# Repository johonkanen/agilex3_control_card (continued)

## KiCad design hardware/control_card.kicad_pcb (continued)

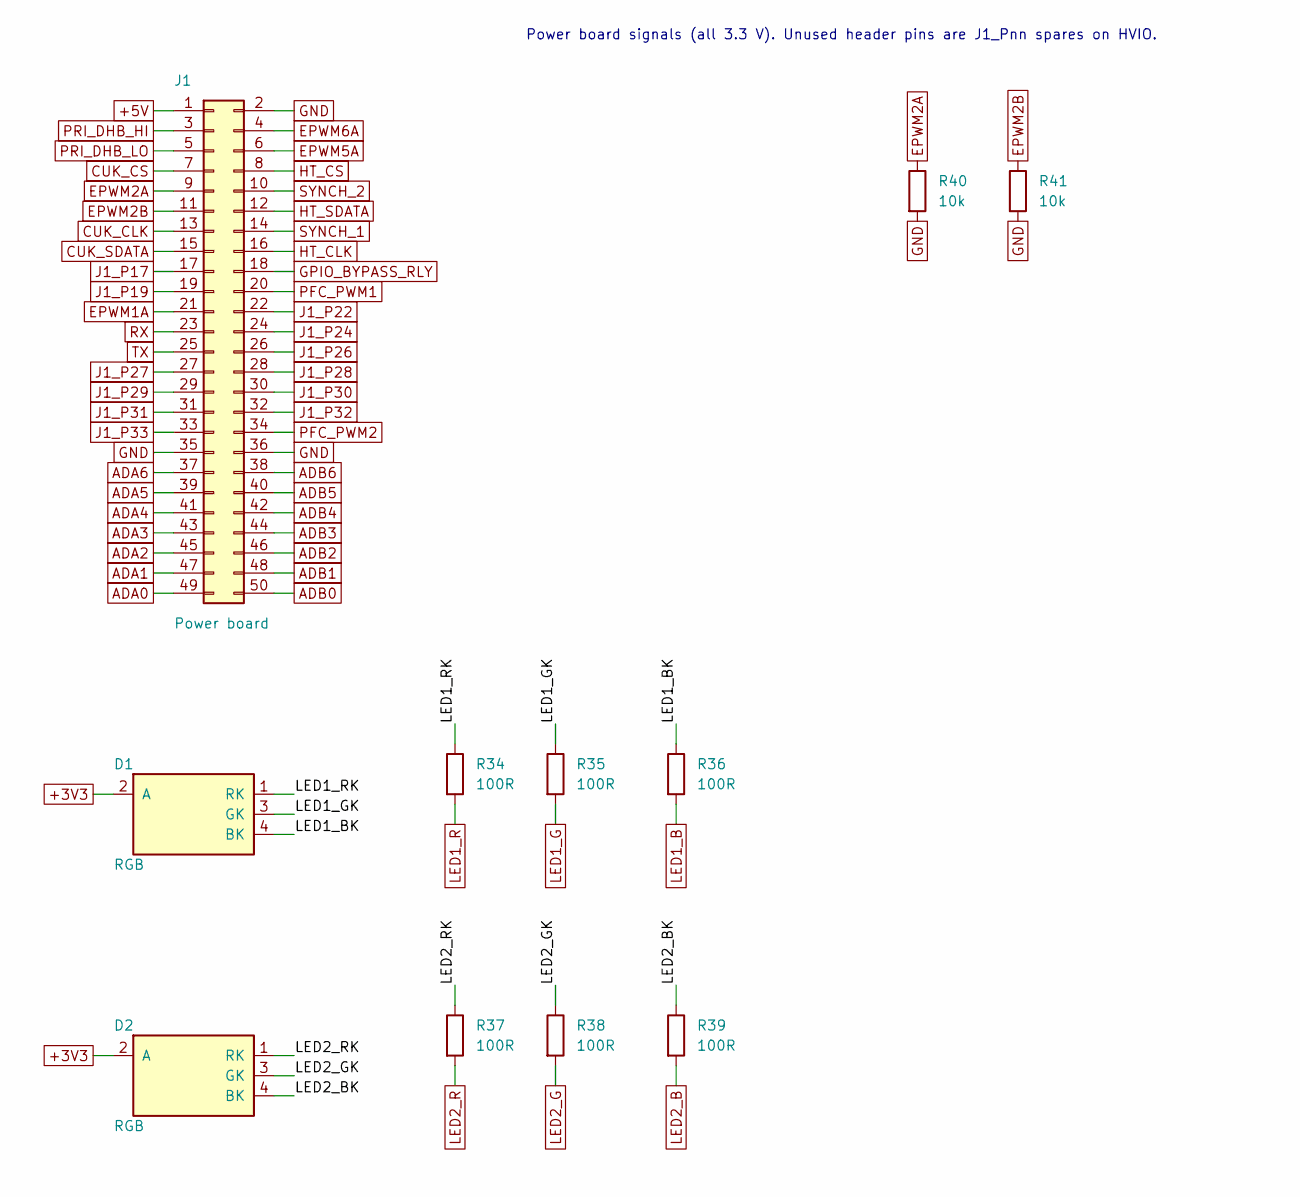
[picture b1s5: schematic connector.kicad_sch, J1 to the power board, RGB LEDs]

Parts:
D1, D2: RGB; LED_RGB_APFA3010_RightAngle; MPN APFA3010LSEEZGKQBKC; LCSC C5393554
J1: Power board; PinHeader_2x25_P1.27mm_Horizontal_U25
R34, R35, R36, R37, R38, R39: 100R; R_0402_1005Metric; MPN 0402WGF1000TCE; LCSC C25076
R40, R41: 10k; R_0201_0603Metric; MPN 0201WMF1002TEE; LCSC C473048

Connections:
+3V3: D1.2 (A), D2.2 (A); also elsewhere on the board
+5V: J1.1; also elsewhere on the board
/Header and LEDs/LED1_BK: D1.4 (BK), R36.1
/Header and LEDs/LED1_GK: D1.3 (GK), R35.1
/Header and LEDs/LED1_RK: D1.1 (RK), R34.1
/Header and LEDs/LED2_BK: D2.4 (BK), R39.1
/Header and LEDs/LED2_GK: D2.3 (GK), R38.1
/Header and LEDs/LED2_RK: D2.1 (RK), R37.1
ADA0: J1.49; also elsewhere on the board
ADA1: J1.47; also elsewhere on the board
ADA2: J1.45; also elsewhere on the board
ADA3: J1.43; also elsewhere on the board
ADA4: J1.41; also elsewhere on the board
ADA5: J1.39; also elsewhere on the board
ADA6: J1.37; also elsewhere on the board
ADB0: J1.50; also elsewhere on the board
ADB1: J1.48; also elsewhere on the board
ADB2: J1.46; also elsewhere on the board
ADB3: J1.44; also elsewhere on the board
ADB4: J1.42; also elsewhere on the board
ADB5: J1.40; also elsewhere on the board
ADB6: J1.38; also elsewhere on the board
CUK_CLK: J1.13; also elsewhere on the board
CUK_CS: J1.7; also elsewhere on the board
CUK_SDATA: J1.15; also elsewhere on the board
EPWM1A: J1.21; also elsewhere on the board
EPWM2A: J1.9, R40.1; also elsewhere on the board
EPWM2B: J1.11, R41.1; also elsewhere on the board
EPWM5A: J1.6; also elsewhere on the board
EPWM6A: J1.4; also elsewhere on the board
GND: J1.2, J1.35, J1.36, R40.2, R41.2; also elsewhere on the board
GPIO_BYPASS_RLY: J1.18; also elsewhere on the board
HT_CLK: J1.16; also elsewhere on the board
HT_CS: J1.8; also elsewhere on the board
HT_SDATA: J1.12; also elsewhere on the board
J1_P17: J1.17; also elsewhere on the board
J1_P19: J1.19; also elsewhere on the board
J1_P22: J1.22; also elsewhere on the board
J1_P24: J1.24; also elsewhere on the board
J1_P26: J1.26; also elsewhere on the board
J1_P27: J1.27; also elsewhere on the board
J1_P28: J1.28; also elsewhere on the board
J1_P29: J1.29; also elsewhere on the board
J1_P30: J1.30; also elsewhere on the board
J1_P31: J1.31; also elsewhere on the board
J1_P32: J1.32; also elsewhere on the board
J1_P33: J1.33; also elsewhere on the board
LED1_B: R36.2; also elsewhere on the board
LED1_G: R35.2; also elsewhere on the board
LED1_R: R34.2; also elsewhere on the board
LED2_B: R39.2; also elsewhere on the board
LED2_G: R38.2; also elsewhere on the board
LED2_R: R37.2; also elsewhere on the board
PFC_PWM1: J1.20; also elsewhere on the board
PFC_PWM2: J1.34; also elsewhere on the board
PRI_DHB_HI: J1.3; also elsewhere on the board
PRI_DHB_LO: J1.5; also elsewhere on the board
RX: J1.23; also elsewhere on the board
SYNCH_1: J1.14; also elsewhere on the board
SYNCH_2: J1.10; also elsewhere on the board
TX: J1.25; also elsewhere on the board

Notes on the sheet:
Power board signals (all 3.3 V). Unused header pins are J1_Pnn spares on HVIO.

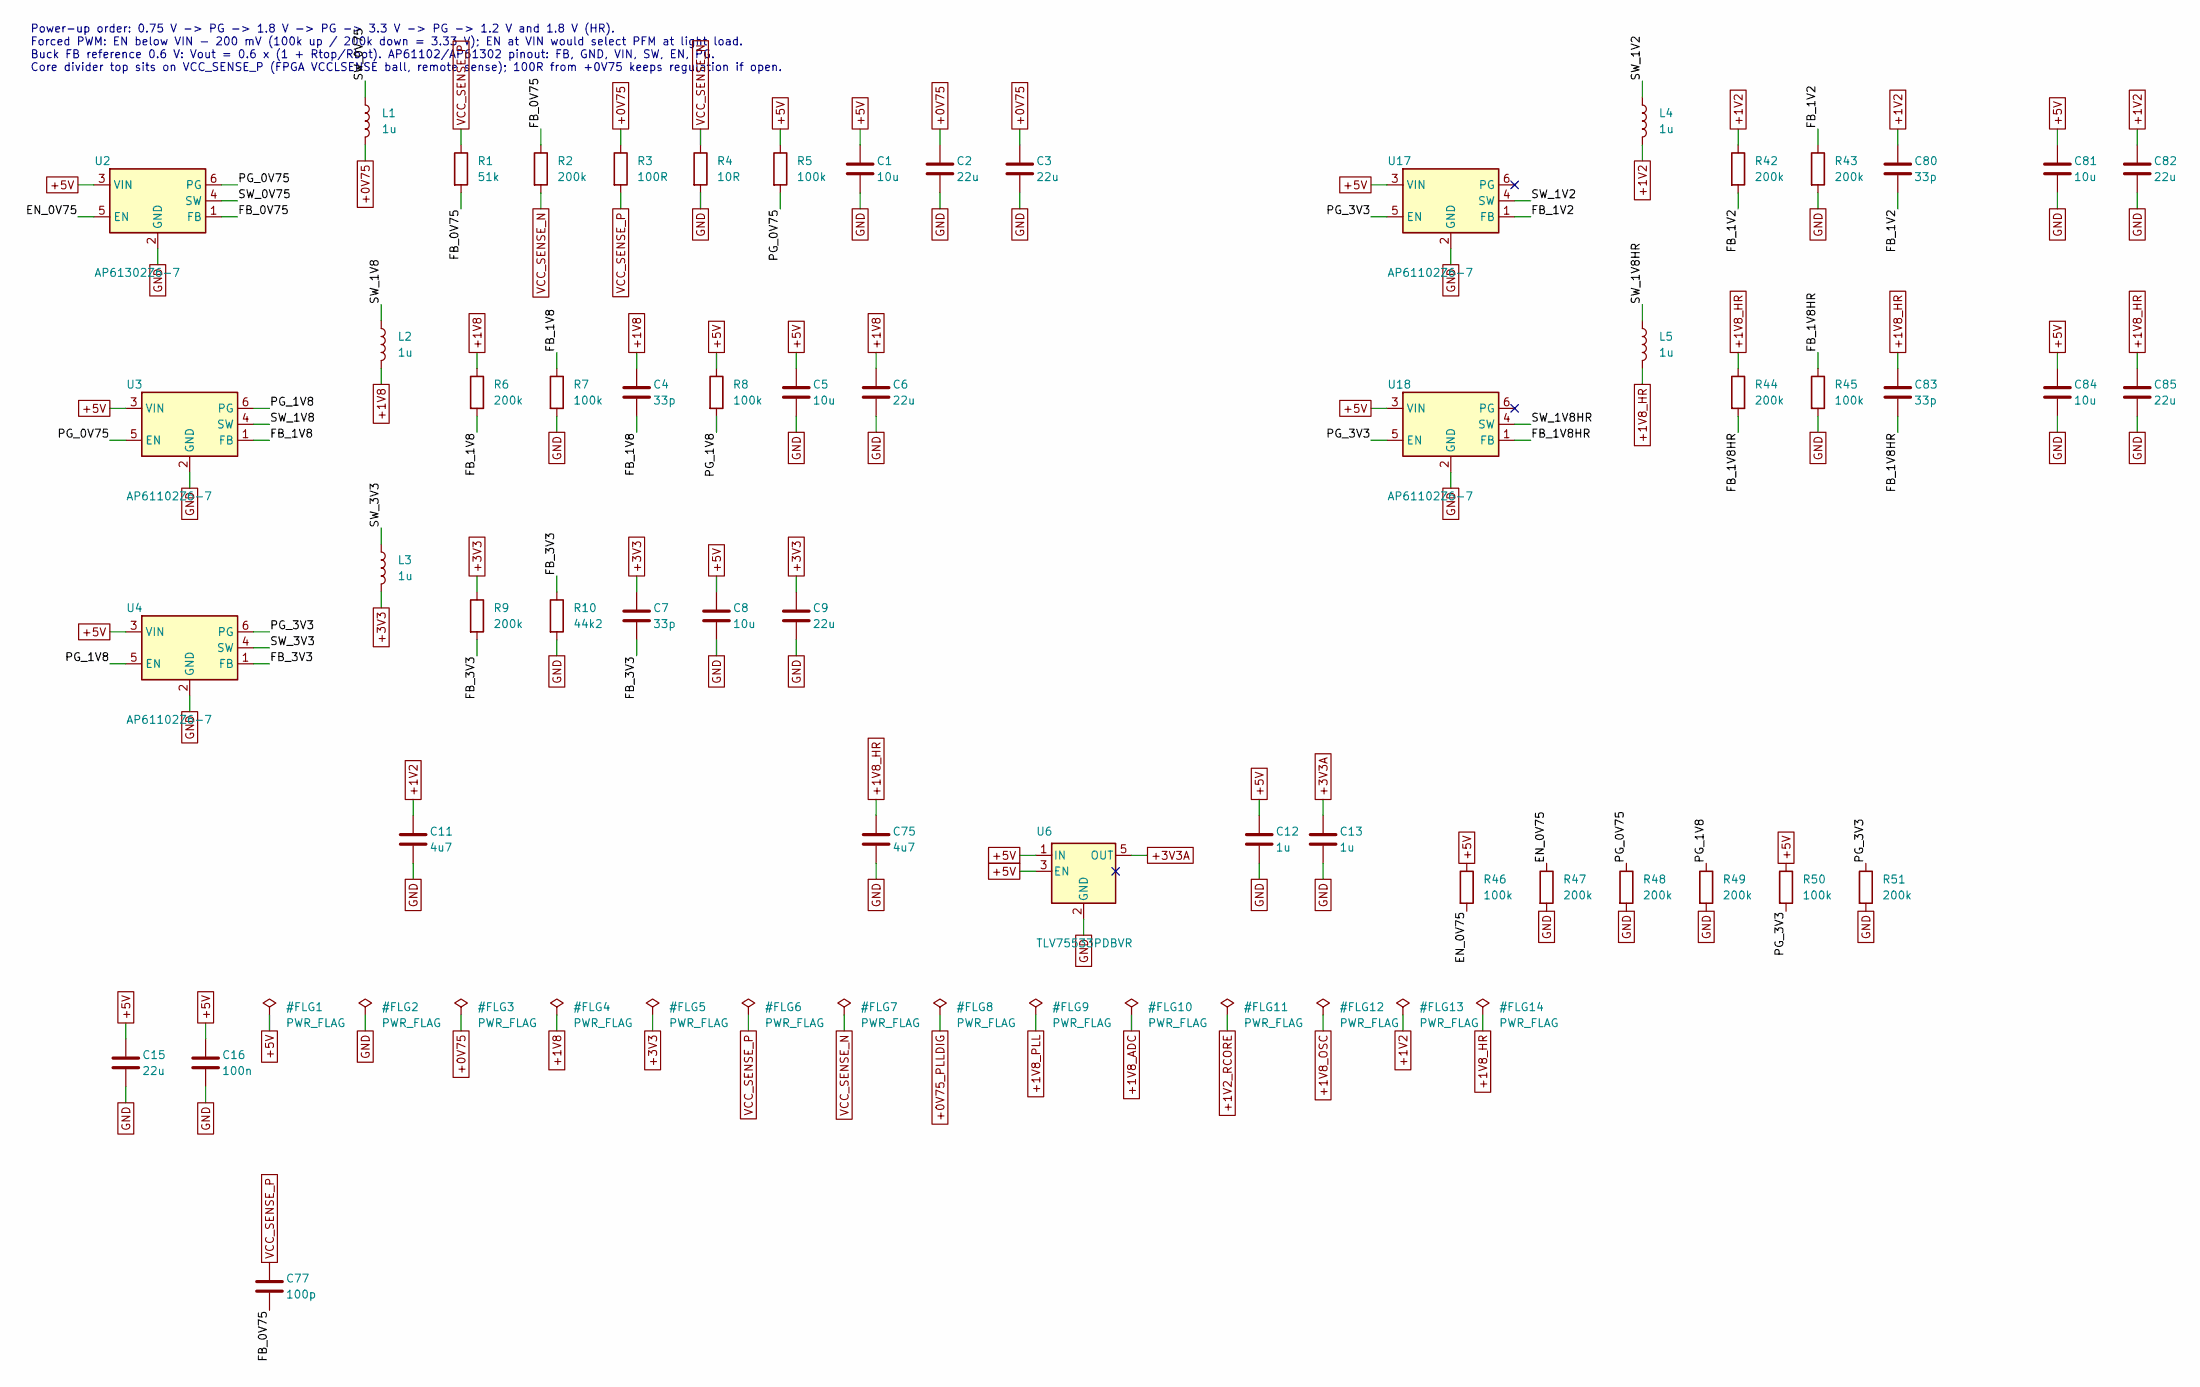
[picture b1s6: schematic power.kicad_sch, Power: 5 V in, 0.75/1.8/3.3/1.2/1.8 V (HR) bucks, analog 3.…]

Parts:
C1, C5, C8, C81, C84: 10u; C_0603_1608Metric; MPN CL10A106KP8NNNC; LCSC C19702
C2, C3, C6, C9, C82, C85: 22u; C_0603_1608Metric; MPN CL10A226MQ8NRNC; LCSC C59461
C4, C7, C80, C83: 33p; C_0402_1005Metric; MPN 0402CG330J500NT; LCSC C1562
C11, C75: 4u7; C_0603_1608Metric; MPN CL10A475KO8NNNC; LCSC C19666
C12, C13: 1u; C_0402_1005Metric; MPN CL05A105KA5NQNC; LCSC C52923
C15: 22u; C_0805_2012Metric; MPN CL21A226MAQNNNE; LCSC C45783
C16: 100n; C_0402_1005Metric; MPN CL05B104KO5NNNC; LCSC C1525
C77: 100p; C_0402_1005Metric; MPN 0402CG101J500NT; LCSC C1546
L1, L2, L3, L4, L5: 1u; L_Cenker_CKCS201610; MPN WPN201610H1R0MT; LCSC C97002
R1: 51k; R_0402_1005Metric; MPN 0402WGF5102TCE; LCSC C25794
R2, R6, R9, R42, R43, R44, R47, R48, R49, R51: 200k; R_0402_1005Metric; MPN 0402WGF2003TCE; LCSC C25764
R3: 100R; R_0402_1005Metric; MPN 0402WGF1000TCE; LCSC C25076
R4: 10R; R_0402_1005Metric; MPN 0402WGF100JTCE; LCSC C25077
R5, R7, R8, R45, R50: 100k; R_0402_1005Metric; MPN 0402WGF1003TCE; LCSC C25741
R10: 44k2; R_0402_1005Metric; MPN 0402WGF4422TCE; LCSC C25895
R46: 100k; R_0201_0603Metric; MPN RC0201FR-07100KL; LCSC C106224
U2: AP61302Z6-7; SOT-563; MPN AP61302Z6-7; LCSC C3193204
U3, U4, U17, U18: AP61102Z6-7; SOT-563; MPN AP61102Z6-7; LCSC C5224055
U6: TLV75533PDBVR; SOT-23-5; MPN TLV75533PDBVR; LCSC C404027

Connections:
+0V75: C2.1, C3.1, L1.2, R3.1; also elsewhere on the board
+1V2: C11.1, C80.1, C82.1, L4.2, R42.1; also elsewhere on the board
+1V8: C4.1, C6.1, L2.2, R6.1; also elsewhere on the board
+1V8_HR: C75.1, C83.1, C85.1, L5.2, R44.1; also elsewhere on the board
+3V3: C7.1, C9.1, L3.2, R9.1; also elsewhere on the board
+3V3A: C13.1, U6.5 (OUT); also elsewhere on the board
+5V: C1.1, C5.1, C8.1, C12.1, C15.1, C16.1, C81.1, C84.1, R5.1, R8.1, R46.1, R50.1, U2.3 (VIN), U3.3 (VIN), U4.3 (VIN), U6.1 (IN), U6.3 (EN), U17.3 (VIN), U18.3 (VIN); also elsewhere on the board
/Power/EN_0V75: R46.2, R47.1, U2.5 (EN)
/Power/FB_0V75: C77.2, R1.2, R2.1, U2.1 (FB)
/Power/FB_1V2: C80.2, R42.2, R43.1, U17.1 (FB)
/Power/FB_1V8: C4.2, R6.2, R7.1, U3.1 (FB)
/Power/FB_1V8HR: C83.2, R44.2, R45.1, U18.1 (FB)
/Power/FB_3V3: C7.2, R9.2, R10.1, U4.1 (FB)
/Power/PG_0V75: R5.2, R48.1, U2.6 (PG), U3.5 (EN)
/Power/PG_1V8: R8.2, R49.1, U3.6 (PG), U4.5 (EN)
/Power/PG_3V3: R50.2, R51.1, U4.6 (PG), U17.5 (EN), U18.5 (EN)
/Power/SW_0V75: L1.1, U2.4 (SW)
/Power/SW_1V2: L4.1, U17.4 (SW)
/Power/SW_1V8: L2.1, U3.4 (SW)
/Power/SW_1V8HR: L5.1, U18.4 (SW)
/Power/SW_3V3: L3.1, U4.4 (SW)
GND: C1.2, C2.2, C3.2, C5.2, C6.2, C8.2, C9.2, C11.2, C12.2, C13.2, C15.2, C16.2, C75.2, C81.2, C82.2, C84.2, C85.2, R4.2, R7.2, R10.2, R43.2, R45.2, R47.2, R48.2, R49.2, R51.2, U2.2 (GND), U3.2 (GND), U4.2 (GND), U6.2 (GND), U17.2 (GND), U18.2 (GND); also elsewhere on the board
VCC_SENSE_N: R2.2, R4.1; also elsewhere on the board
VCC_SENSE_P: C77.1, R1.1, R3.2; also elsewhere on the board

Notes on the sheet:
Power-up order: 0.75 V -> PG -> 1.8 V -> PG -> 3.3 V -> PG -> 1.2 V and 1.8 V (HR). Forced PWM: EN below VIN - 200 mV (100k up / 200k down = 3.33 V); EN at VIN would select PFM at light load. Buck FB reference 0.6 V: Vout = 0.6 x (1 + Rtop/Rbot). AP61102/AP61302 pinout: FB, GND, VIN, SW, EN, PG. Co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

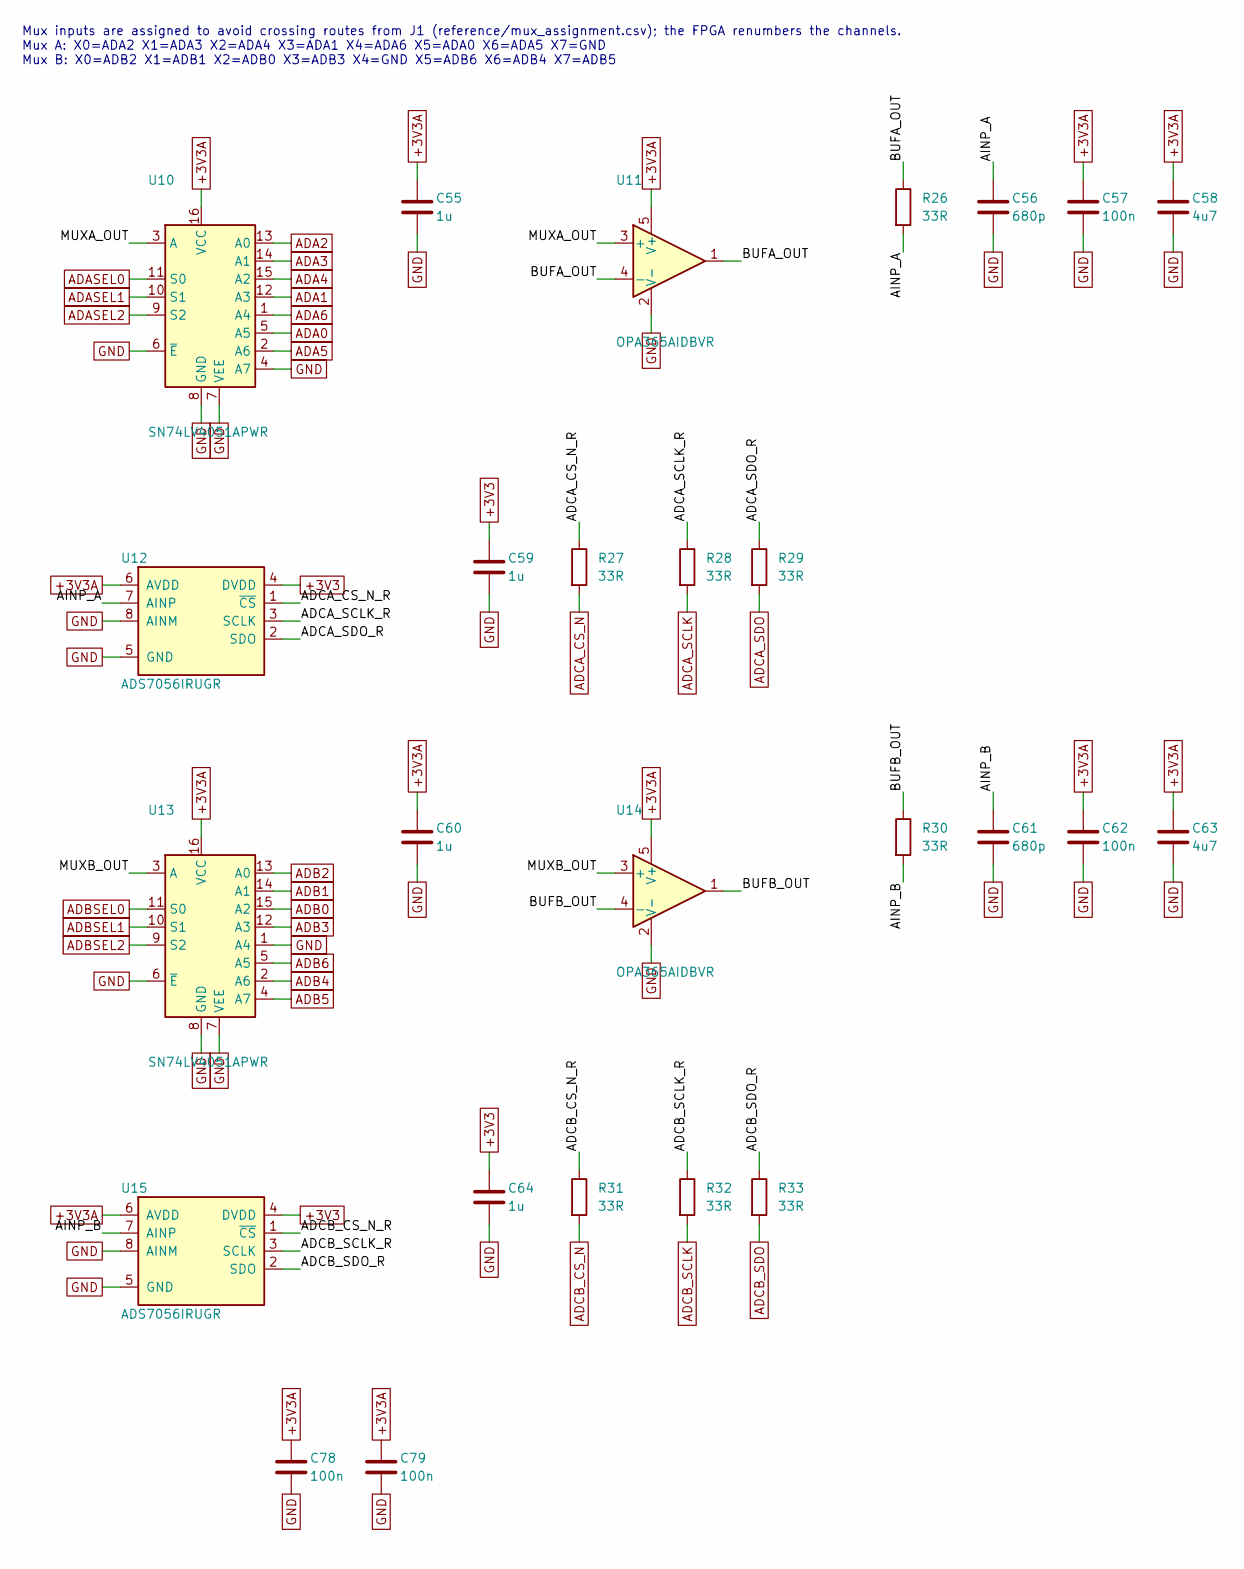
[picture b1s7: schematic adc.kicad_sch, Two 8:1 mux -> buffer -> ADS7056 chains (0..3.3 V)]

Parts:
C55, C59, C60, C64: 1u; C_0402_1005Metric; MPN CL05A105KA5NQNC; LCSC C52923
C56, C61: 680p; C_0402_1005Metric; MPN CC0402JRNPO9BN681; LCSC C113781
C57, C62, C78, C79: 100n; C_0402_1005Metric; MPN CL05B104KO5NNNC; LCSC C1525
C58, C63: 4u7; C_0603_1608Metric; MPN CL10A475KO8NNNC; LCSC C19666
R26, R30: 33R; R_0402_1005Metric; MPN 0402WGF330JTCE; LCSC C25105
R27, R28, R29, R32, R33: 33R; R_0201_0603Metric; MPN RC-01W33R0FT; LCSC C320843
R31: 33R; C_0201_0603Metric; MPN RC-01W33R0FT; LCSC C320843
U10, U13: SN74LV4051APWR; TSSOP-16_4.4x5mm_P0.65mm; MPN SN74LV4051APWR; LCSC C7793
U11, U14: OPA365AIDBVR; SOT-23-5; MPN OPA365AIDBVR; LCSC C96626
U12, U15: ADS7056IRUGR; Texas_UQFN-8_1.5x1.5mm_P0.5mm; MPN ADS7056IRUGR; LCSC C2669798

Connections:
+3V3: C59.1, C64.1, U12.4 (DVDD), U15.4 (DVDD); also elsewhere on the board
+3V3A: C55.1, C57.1, C58.1, C60.1, C62.1, C63.1, C78.1, C79.1, U10.16 (VCC), U11.5 (V+), U12.6 (AVDD), U13.16 (VCC), U14.5 (V+), U15.6 (AVDD); also elsewhere on the board
/ADC/ADCA_CS_N_R: R27.1, U12.1 (~CS)
/ADC/ADCA_SCLK_R: R28.1, U12.3 (SCLK)
/ADC/ADCA_SDO_R: R29.1, U12.2 (SDO)
/ADC/ADCB_CS_N_R: R31.1, U15.1 (~CS)
/ADC/ADCB_SCLK_R: R32.1, U15.3 (SCLK)
/ADC/ADCB_SDO_R: R33.1, U15.2 (SDO)
/ADC/AINP_A: C56.1, R26.2, U12.7 (AINP)
/ADC/AINP_B: C61.1, R30.2, U15.7 (AINP)
/ADC/BUFA_OUT: R26.1, U11.1, U11.4 (-)
/ADC/BUFB_OUT: R30.1, U14.1, U14.4 (-)
/ADC/MUXA_OUT: U10.3 (A), U11.3 (+)
/ADC/MUXB_OUT: U13.3 (A), U14.3 (+)
ADA0: U10.5 (A5); also elsewhere on the board
ADA1: U10.12 (A3); also elsewhere on the board
ADA2: U10.13 (A0); also elsewhere on the board
ADA3: U10.14 (A1); also elsewhere on the board
ADA4: U10.15 (A2); also elsewhere on the board
ADA5: U10.2 (A6); also elsewhere on the board
ADA6: U10.1 (A4); also elsewhere on the board
ADASEL0: U10.11 (S0); also elsewhere on the board
ADASEL1: U10.10 (S1); also elsewhere on the board
ADASEL2: U10.9 (S2); also elsewhere on the board
ADB0: U13.15 (A2); also elsewhere on the board
ADB1: U13.14 (A1); also elsewhere on the board
ADB2: U13.13 (A0); also elsewhere on the board
ADB3: U13.12 (A3); also elsewhere on the board
ADB4: U13.2 (A6); also elsewhere on the board
ADB5: U13.4 (A7); also elsewhere on the board
ADB6: U13.5 (A5); also elsewhere on the board
ADBSEL0: U13.11 (S0); also elsewhere on the board
ADBSEL1: U13.10 (S1); also elsewhere on the board
ADBSEL2: U13.9 (S2); also elsewhere on the board
ADCA_CS_N: R27.2; also elsewhere on the board
ADCA_SCLK: R28.2; also elsewhere on the board
ADCA_SDO: R29.2; also elsewhere on the board
ADCB_CS_N: R31.2; also elsewhere on the board
ADCB_SCLK: R32.2; also elsewhere on the board
ADCB_SDO: R33.2; also elsewhere on the board
GND: C55.2, C56.2, C57.2, C58.2, C59.2, C60.2, C61.2, C62.2, C63.2, C64.2, C78.2, C79.2, U10.4 (A7), U10.6 (~E), U10.7 (VEE), U10.8 (GND), U11.2 (V-), U12.5 (GND), U12.8 (AINM), U13.1 (A4), U13.6 (~E), U13.7 (VEE), U13.8 (GND), U14.2 (V-), U15.5 (GND), U15.8 (AINM); also elsewhere on the board

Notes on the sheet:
Mux inputs are assigned to avoid crossing routes from J1 (reference/mux_assignment.csv); the FPGA renumbers the channels. Mux A: X0=ADA2 X1=ADA3 X2=ADA4 X3=ADA1 X4=ADA6 X5=ADA0 X6=ADA5 X7=GND Mux B: X0=ADB2 X1=ADB1 X2=ADB0 X3=ADB3 X4=GND X5=ADB6 X6=ADB4 X7=ADB5

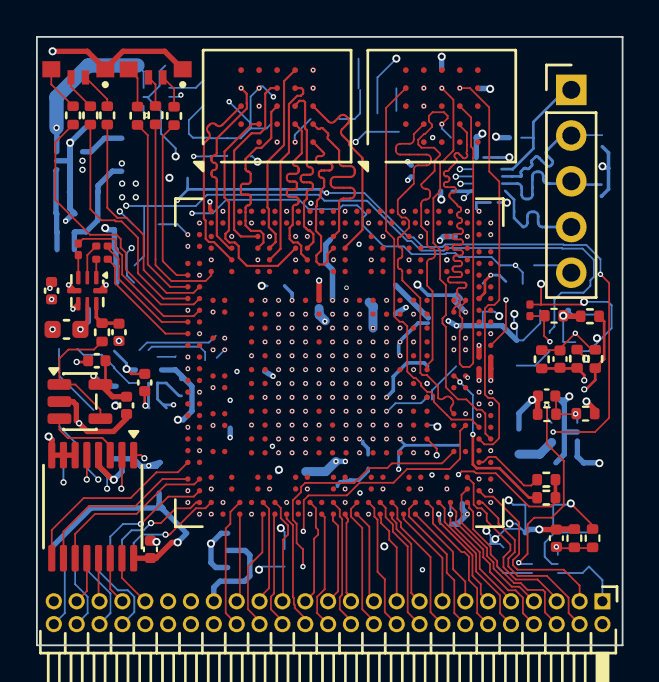
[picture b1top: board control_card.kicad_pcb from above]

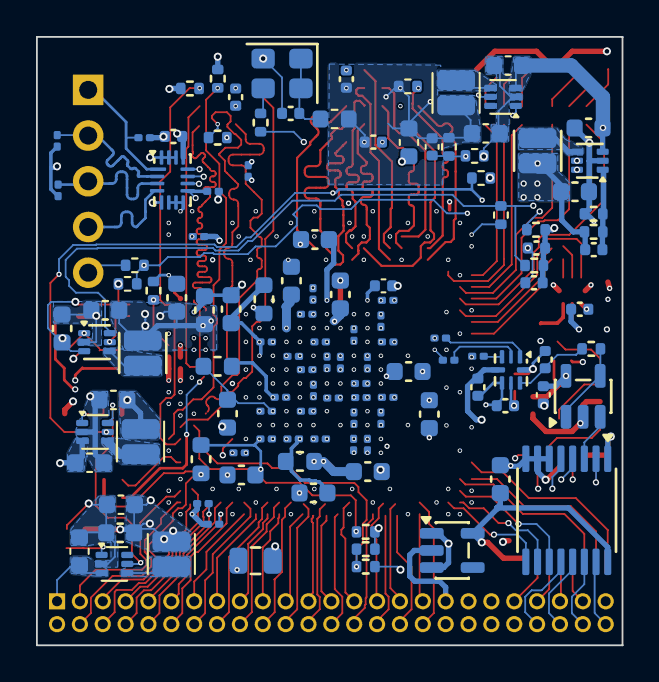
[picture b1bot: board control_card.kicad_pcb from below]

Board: 6 copper layers, 32.5 x 33.8 mm, 164 parts (122 on the bottom side), 145 nets.

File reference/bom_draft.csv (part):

ref,value,footprint,lcsc,mpn,dnp
C1,10u,Capacitor_SMD:C_0603_1608Metric,C19702,CL10A106KP8NNNC,False
C2,22u,Capacitor_SMD:C_0603_1608Metric,C59461,CL10A226MQ8NRNC,False
C3,22u,Capacitor_SMD:C_0603_1608Metric,C59461,CL10A226MQ8NRNC,False
C4,22p,Capacitor_SMD:C_0402_1005Metric,C1555,0402CG220J500NT,False
C5,10u,Capacitor_SMD:C_0603_1608Metric,C19702,CL10A106KP8NNNC,False
C6,22u,Capacitor_SMD:C_0603_1608Metric,C59461,CL10A226MQ8NRNC,False
C7,22p,Capacitor_SMD:C_0402_1005Metric,C1555,0402CG220J500NT,False
C8,10u,Capacitor_SMD:C_0603_1608Metric,C19702,CL10A106KP8NNNC,False
C9,22u,Capacitor_SMD:C_0603_1608Metric,C59461,CL10A226MQ8NRNC,False
C10,1u,Capacitor_SMD:C_0402_1005Metric,C52923,CL05A105KA5NQNC,False
C11,4u7,Capacitor_SMD:C_0603_1608Metric,C19666,CL10A475KO8NNNC,False
C12,1u,Capacitor_SMD:C_0402_1005Metric,C52923,CL05A105KA5NQNC,False
C13,1u,Capacitor_SMD:C_0402_1005Metric,C52923,CL05A105KA5NQNC,False
C14,22u,Capacitor_SMD:C_0805_2012Metric,C45783,CL21A226MAQNNNE,False
C15,22u,Capacitor_SMD:C_0805_2012Metric,C45783,CL21A226MAQNNNE,False
C16,100n,Capacitor_SMD:C_0402_1005Metric,C1525,CL05B104KO5NNNC,False
C17,22u,Capacitor_SMD:C_0603_1608Metric,C59461,CL10A226MQ8NRNC,False
C18,22u,Capacitor_SMD:C_0603_1608Metric,C59461,CL10A226MQ8NRNC,False
C19,10u,Capacitor_SMD:C_0603_1608Metric,C19702,CL10A106KP8NNNC,False
C20,10u,Capacitor_SMD:C_0603_1608Metric,C19702,CL10A106KP8NNNC,False
C21,4u7,Capacitor_SMD:C_0201_0603Metric,C335103,GRM035R60J475ME15D,False
C22,4u7,Capacitor_SMD:C_0201_0603Metric,C335103,GRM035R60J475ME15D,False
C23,4u7,Capacitor_SMD:C_0201_0603Metric,C335103,GRM035R60J475ME15D,False
C24,1u,Capacitor_SMD:C_0201_0603Metric,C170152,CL03A105MQ3CSNC,False
C25,1u,Capacitor_SMD:C_0201_0603Metric,C170152,CL03A105MQ3CSNC,False
C26,1u,Capacitor_SMD:C_0201_0603Metric,C170152,CL03A105MQ3CSNC,False
C27,1u,Capacitor_SMD:C_0201_0603Metric,C170152,CL03A105MQ3CSNC,False
C28,1u,Capacitor_SMD:C_0201_0603Metric,C170152,CL03A105MQ3CSNC,False
C29,10u,Capacitor_SMD:C_0603_1608Metric,C19702,CL10A106KP8NNNC,False
C30,4u7,Capacitor_SMD:C_0201_0603Metric,C335103,GRM035R60J475ME15D,False
C31,4u7,Capacitor_SMD:C_0201_0603Metric,C335103,GRM035R60J475ME15D,False
C32,1u,Capacitor_SMD:C_0201_0603Metric,C170152,CL03A105MQ3CSNC,False
C33,1u,Capacitor_SMD:C_0201_0603Metric,C170152,CL03A105MQ3CSNC,False
C34,1u,Capacitor_SMD:C_0201_0603Metric,C170152,CL03A105MQ3CSNC,False
C35,1u,Capacitor_SMD:C_0201_0603Metric,C170152,CL03A105MQ3CSNC,False
C36,1u,Capacitor_SMD:C_0201_0603Metric,C170152,CL03A105MQ3CSNC,False
C37,10u,Capacitor_SMD:C_0603_1608Metric,C19702,CL10A106KP8NNNC,False
C38,1u,Capacitor_SMD:C_0201_0603Metric,C170152,CL03A105MQ3CSNC,False
C39,1u,Capacitor_SMD:C_0201_0603Metric,C170152,CL03A105MQ3CSNC,False
C40,1u,Capacitor_SMD:C_0201_0603Metric,C170152,CL03A105MQ3CSNC,False
C41,1u,Capacitor_SMD:C_0201_0603Metric,C170152,CL03A105MQ3CSNC,False
C42,1u,Capacitor_SMD:C_0201_0603Metric,C170152,CL03A105MQ3CSNC,False
C43,1u,Capacitor_SMD:C_0201_0603Metric,C170152,CL03A105MQ3CSNC,False
C44,4u7,Capacitor_SMD:C_0603_1608Metric,C19666,CL10A475KO8NNNC,False
C45,4u7,Capacitor_SMD:C_0201_0603Metric,C335103,GRM035R60J475ME15D,False
C46,1u,Capacitor_SMD:C_0201_0603Metric,C170152,CL03A105MQ3CSNC,False
C47,100n,Capacitor_SMD:C_0402_1005Metric,C1525,CL05B104KO5NNNC,False
C48,1u,Capacitor_SMD:C_0402_1005Metric,C52923,CL05A105KA5NQNC,False
C49,100n,Capacitor_SMD:C_0201_0603Metric,C49062,CL03A104KP3NNNC,False
C50,100n,Capacitor_SMD:C_0201_0603Metric,C49062,CL03A104KP3NNNC,False
C51,100n,Capacitor_SMD:C_0402_1005Metric,C1525,CL05B104KO5NNNC,False
C52,100n,Capacitor_SMD:C_0402_1005Metric,C1525,CL05B104KO5NNNC,False
C53,1u,Capacitor_SMD:C_0402_1005Metric,C52923,CL05A105KA5NQNC,False
C54,470n,Capacitor_SMD:C_0402_1005Metric,C47339,CL05A474KP5NNNC,False
C55,1u,Capacitor_SMD:C_0402_1005Metric,C52923,CL05A105KA5NQNC,False
C56,680p,Capacitor_SMD:C_0402_1005Metric,C301953,0402CG681J500NT,False
C57,100n,Capacitor_SMD:C_0402_1005Metric,C1525,CL05B104KO5NNNC,False
C58,4u7,Capacitor_SMD:C_0603_1608Metric,C19666,CL10A475KO8NNNC,False
C59,1u,Capacitor_SMD:C_0402_1005Metric,C52923,CL05A105KA5NQNC,False
C60,1u,Capacitor_SMD:C_0402_1005Metric,C52923,CL05A105KA5NQNC,False
C61,680p,Capacitor_SMD:C_0402_1005Metric,C301953,0402CG681J500NT,False
C62,100n,Capacitor_SMD:C_0402_1005Metric,C1525,CL05B104KO5NNNC,False
C63,4u7,Capacitor_SMD:C_0603_1608Metric,C19666,CL10A475KO8NNNC,False
C64,1u,Capacitor_SMD:C_0402_1005Metric,C52923,CL05A105KA5NQNC,False
C65,47u,Capacitor_SMD:C_0603_1608Metric,C6119831,CGA0603X5R476M6R3JT,False
C66,1u,Capacitor_SMD:C_0201_0603Metric,C170152,CL03A105MQ3CSNC,False
C67,47u,Capacitor_SMD:C_0603_1608Metric,C6119831,CGA0603X5R476M6R3JT,False
C68,1u,Capacitor_SMD:C_0201_0603Metric,C170152,CL03A105MQ3CSNC,False
C69,47u,Capacitor_SMD:C_0603_1608Metric,C6119831,CGA0603X5R476M6R3JT,False
C70,1u,Capacitor_SMD:C_0201_0603Metric,C170152,CL03A105MQ3CSNC,False
C71,47u,Capacitor_SMD:C_0603_1608Metric,C6119831,CGA0603X5R476M6R3JT,False
C72,1u,Capacitor_SMD:C_0201_0603Metric,C170152,CL03A105MQ3CSNC,False
C73,1u,Capacitor_SMD:C_0201_0603Metric,C170152,CL03A105MQ3CSNC,False
C74,1u,Capacitor_SMD:C_0402_1005Metric,C52923,CL05A105KA5NQNC,False
C75,4u7,Capacitor_SMD:C_0603_1608Metric,C19666,CL10A475KO8NNNC,False
C76,1u,Capacitor_SMD:C_0201_0603Metric,C170152,CL03A105MQ3CSNC,False
D1,RGB,control_card:LED_RGB_APFA3010_RightAngle,C5393554,APFA3010LSEEZGKQBKC,False
D2,RGB,control_card:LED_RGB_APFA3010_RightAngle,C5393554,APFA3010LSEEZGKQBKC,False
FB1,120R@100MHz,Inductor_SMD:L_0603_1608Metric,C14709,BLM18PG121SN1D,False
FB2,120R@100MHz,Inductor_SMD:L_0603_1608Metric,C14709,BLM18PG121SN1D,False
FB3,120R@100MHz,Inductor_SMD:L_0603_1608Metric,C14709,BLM18PG121SN1D,False
FB4,120R@100MHz,Inductor_SMD:L_0603_1608Metric,C14709,BLM18PG121SN1D,False
FB5,120R@100MHz,Inductor_SMD:L_0603_1608Metric,C14709,BLM18PG121SN1D,False
J1,Power board,control_card:PinHeader_2x25_P1.27mm_Horizontal_U25,,,False
J2,JTAG,Connector_PinHeader_2.54mm:PinHeader_1x05_P2.54mm_Vertical,,,False
L1,1u,Inductor_SMD:L_Cenker_CKCS201610,C97002,WPN201610H1R0MT,False
L2,1u,Inductor_SMD:L_Cenker_CKCS201610,C97002,WPN201610H1R0MT,False
L3,1u,Inductor_SMD:L_Cenker_CKCS201610,C97002,WPN201610H1R0MT,False
R1,49k9,Resistor_SMD:R_0402_1005Metric,C25897,0402WGF4992TCE,False
R2,200k,Resistor_SMD:R_0402_1005Metric,C25764,0402WGF2003TCE,False
R3,100R,Resistor_SMD:R_0402_1005Metric,C25076,0402WGF1000TCE,False
R4,10R,Resistor_SMD:R_0402_1005Metric,C25077,0402WGF100JTCE,False
R5,100k,Resistor_SMD:R_0402_1005Metric,C25741,0402WGF1003TCE,False
R6,200k,Resistor_SMD:R_0402_1005Metric,C25764,0402WGF2003TCE,False
R7,100k,Resistor_SMD:R_0402_1005Metric,C25741,0402WGF1003TCE,False
R8,100k,Resistor_SMD:R_0402_1005Metric,C25741,0402WGF1003TCE,False
R9,200k,Resistor_SMD:R_0402_1005Metric,C25764,0402WGF2003TCE,False
R10,44k2,Resistor_SMD:R_0402_1005Metric,C25895,0402WGF4422TCE,False
R11,4k7,Resistor_SMD:R_0402_1005Metric,C25900,0402WGF4701TCE,False
R12,4k7,Resistor_SMD:R_0402_1005Metric,C25900,0402WGF4701TCE,False
R13,4k7,Resistor_SMD:R_0402_1005Metric,C25900,0402WGF4701TCE,False
R14,4k7,Resistor_SMD:R_0402_1005Metric,C25900,0402WGF4701TCE,True
R15,10k,Resistor_SMD:R_0402_1005Metric,C25744,0402WGF1002TCE,False
R16,10k,Resistor_SMD:R_0402_1005Metric,C25744,0402WGF1002TCE,False
R17,10k,Resistor_SMD:R_0402_1005Metric,C25744,0402WGF1002TCE,False
R18,10k,Resistor_SMD:R_0402_1005Metric,C25744,0402WGF1002TCE,False
R19,2k,Resistor_SMD:R_0402_1005Metric,C4109,0402WGF2001TCE,False
R20,1k,Resistor_SMD:R_0201_0603Metric,C270365,0201WMF1001TEE,False
R21,10k,Resistor_SMD:R_0201_0603Metric,C473048,0201WMF1002TEE,False
R22,10k,Resistor_SMD:R_0201_0603Metric,C473048,0201WMF1002TEE,False
R23,10k,Resistor_SMD:R_0201_0603Metric,C473048,0201WMF1002TEE,False
R24,10k,Resistor_SMD:R_0402_1005Metric,C25744,0402WGF1002TCE,False
R25,33R,Resistor_SMD:R_0402_1005Metric,C25105,0402WGF330JTCE,False
R26,33R,Resistor_SMD:R_0402_1005Metric,C25105,0402WGF330JTCE,False
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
